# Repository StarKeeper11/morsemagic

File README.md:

Morse Magic - The Swiss Army Knife for everything Morse Code!
(for fellow radio operators)

It can:
* Read CW Input from a Paddle
* Read and Decode Audio
* Send CW from a keyboard via BLE
* Fix your timing
* Connect to most virtual CW Bands
* Auto - transmit callsign/whatever you want

All of this, either standalone or connected to your device of choice!
It also has built in capacitive touch paddles, for backups/emergencies!
Controlled via built-in display and paddles or via bluetooth (html app required)

This is also my first PCB and first venture into designing electronics.

This is a WIP repo: I will update with code files and the likes in the future

Designed and made during Hack Club's Half Life Week 1 (and probably more to follow)

If you know where the quote is from, then you are a real one

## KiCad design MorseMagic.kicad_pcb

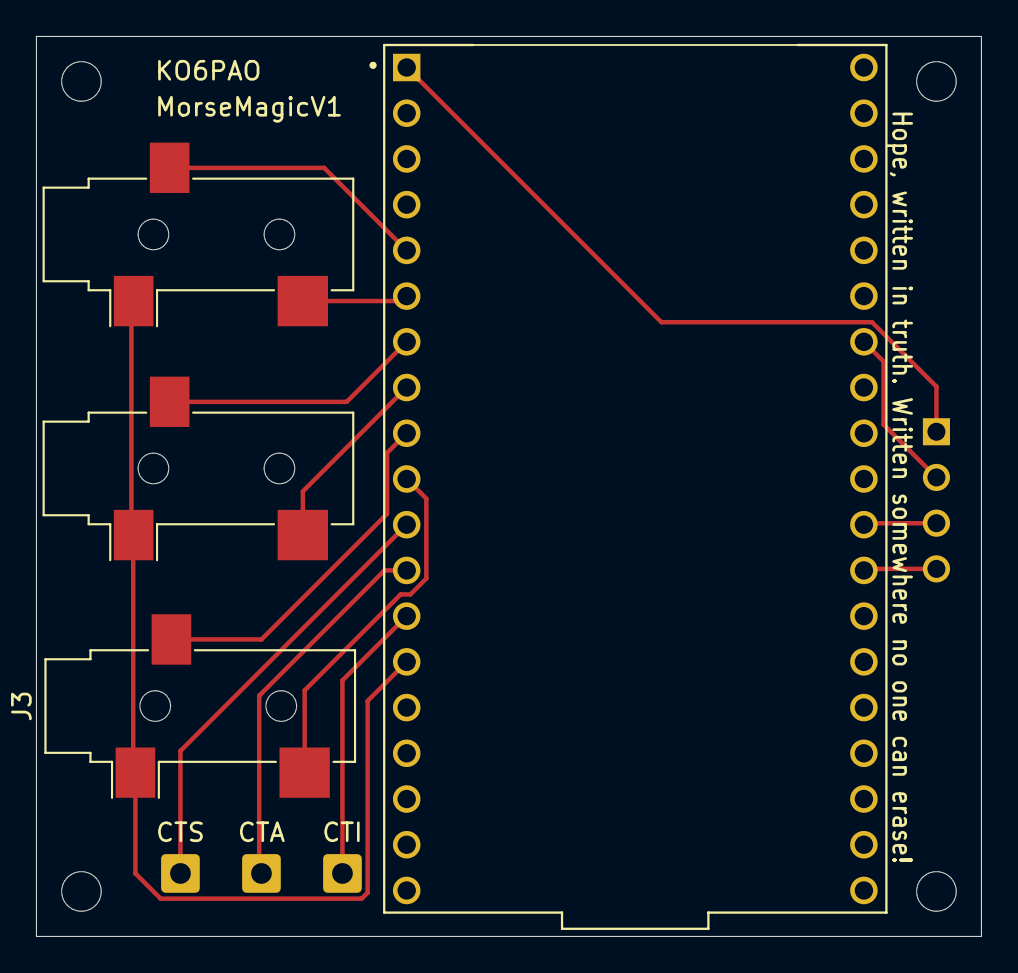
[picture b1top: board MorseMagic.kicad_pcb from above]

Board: 2 copper layers, 52.5 x 50.0 mm, 7 parts (0 on the bottom side), 10 nets.

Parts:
CTA: CTDah; SolderWire-0.5sqmm_1x01_D0.9mm_OD2.1mm
CTI: CTDit; SolderWire-0.5sqmm_1x01_D0.9mm_OD2.1mm
CTS: CTStraight; SolderWire-0.5sqmm_1x01_D0.9mm_OD2.1mm
J3: AudioIn; Jack_3.5mm_CUI_SJ-3523-SMT_Horizontal
J4, J5: CWIn; Jack_3.5mm_CUI_SJ-3523-SMT_Horizontal
U3: ESP32-DevKitC; MODULE_ESP32-DEVKITC

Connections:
unnamed: J3.S, J4.S, J5.S, U3.14 (GND), U3.32 (GND), U3.38 (GND)
unnamed: J5.T, U3.8 (32K_XN/GPIO33/ADC1_CH5)
unnamed: J5.R, U3.7 (32K_XP/GPIO32/ADC1_CH4)
unnamed: CTS.1 (1_1), U3.11 (ADC2_CH7/GPIO27)
unnamed: J3.R, U3.9 (DAC_1/ADC2_CH8/GPIO25)
unnamed: J3.T, U3.10 (DAC_2/ADC2_CH9/GPIO26)
unnamed: CTI.1 (1_1), U3.13 (MTDI/GPIO12/ADC2_CH5)
unnamed: CTA.1 (1_1), U3.12 (MTMS/GPIO14/ADC2_CH6)
unnamed: J4.R, U3.5 (VDET_1/GPIO34/ADC1_CH6)
unnamed: J4.T, U3.6 (VDET_2/GPIO35/ADC1_CH7)

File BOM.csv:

"Reference","Qty","Value","DNP","Exclude from BOM","Exclude from Board","Exclude from Simulation","Exclude from Position Files","Footprint","Datasheet"
"DS1","1","OLED_128X64_1.3_I2C","","","","","${EXCLUDE_FROM_POS_FILES}","OLED_128X64_1.3_I2C (1):LCD_OLED_128X64_1.3_I2C",""
"J3","1","AudioIn","","","","","${EXCLUDE_FROM_POS_FILES}","Connector_Audio:Jack_3.5mm_CUI_SJ-3523-SMT_Horizontal",""
"J4,J5","2","CWIn","","","","","${EXCLUDE_FROM_POS_FILES}","Connector_Audio:Jack_3.5mm_CUI_SJ-3523-SMT_Horizontal",""
"U3","1","ESP32-DevKitC","","","","","${EXCLUDE_FROM_POS_FILES}","ESP32-DEVKITC:MODULE_ESP32-DEVKITC","https://docs.espressif.com/projects/esp-idf/zh_CN/latest/esp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"
